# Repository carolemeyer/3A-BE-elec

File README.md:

# 3A-BE-elec
BE d'électronique de 3AE du binôme : Carole Meyer et Louis Nouguerède

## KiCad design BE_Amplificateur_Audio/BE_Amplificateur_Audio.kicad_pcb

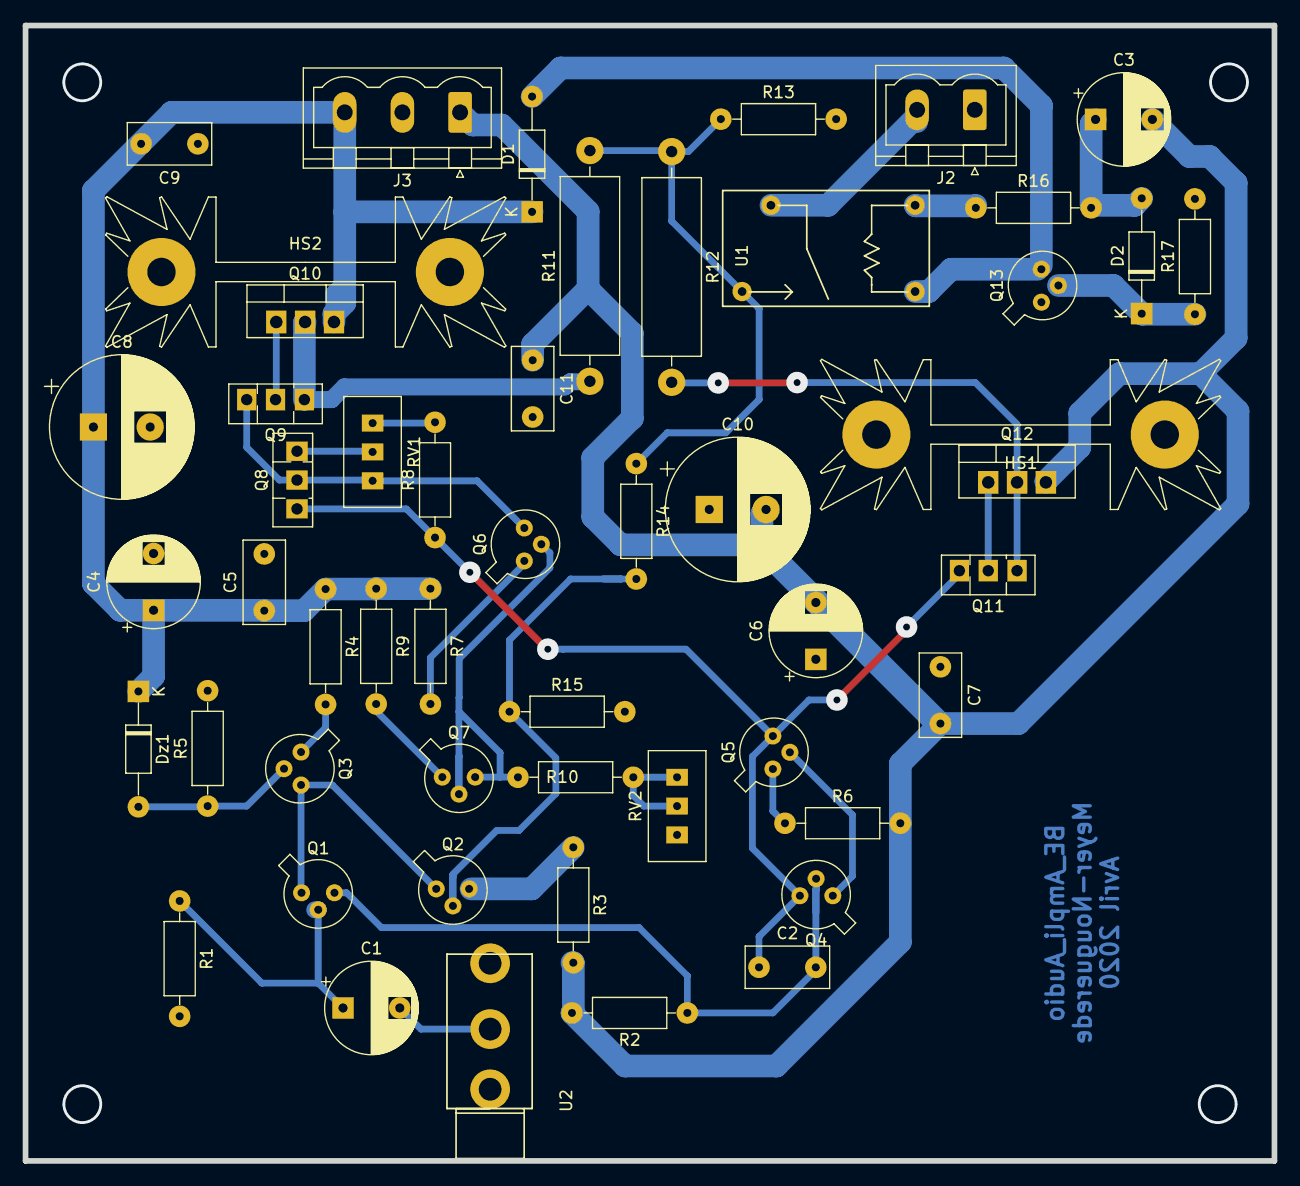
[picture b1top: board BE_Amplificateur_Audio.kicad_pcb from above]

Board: 2 copper layers, 110.0 x 100.0 mm, 52 parts (0 on the bottom side), 31 nets.

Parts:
C1, C3: 47µ; CP_Radial_D8.0mm_P5.00mm
C2: C; C_Rect_L7.2mm_W3.5mm_P5.00mm_FKS2_FKP2_MKS2_MKP2
C4, C6: 10µ; CP_Radial_D8.0mm_P5.00mm
C5, C7, C9, C11: 100n; C_Rect_L7.2mm_W3.5mm_P5.00mm_FKS2_FKP2_MKS2_MKP2
C8, C10: 470µ; CP_Radial_D12.5mm_P5.00mm
D1, D2: 1N4148; D_DO-35_SOD27_P10.16mm_Horizontal
Dz1: BZX55C5V1; D_DO-35_SOD27_P10.16mm_Horizontal
HS1, HS2: Heatsink; Heatsink_Fischer_SK104-STC-STIC_35x13mm_2xDrill2.5mm
J2: Conn_01x02; PhoenixContact_MSTBVA_2,5_2-G-5,08_1x02_P5.08mm_Vertical
J3: Conn_01x03; PhoenixContact_MSTBVA_2,5_3-G-5,08_1x03_P5.08mm_Vertical
Q1, Q2, Q3, Q6, Q7: 2N2907; TO-18-3
Q4, Q5, Q13: 2N2222; TO-18-3
Q8, Q9: BD139; TO-126-3_Vertical
Q10: TIP32; TO-220-3_Vertical
Q11: BD138; TO-126-3_Vertical
Q12: TIP31; TO-220-3_Vertical
R1, R2, R3, R4, R5, R6, R7, R8, R9, R10, R13, R14, R15, R16, R17: R; R_Axial_DIN0207_L6.3mm_D2.5mm_P10.16mm_Horizontal
R11, R12: R; R_Axial_DIN0516_L15.5mm_D5.0mm_P20.32mm_Horizontal
RV1, RV2: R_POT; Potentiometer_Bourns_3296W_Vertical
U1: Relay_1CT; RelayBE
U2: Jack_Mono; Jack_35RAPC2AV

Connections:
+12V: C4.1, C5.1, C8.1, C9.2, D1.1, Dz1.1, J3.3, Q10.3, R4.1, R7.1, R9.1
-12V: C3.2, C6.2, C7.2, C10.2, C11.1, J3.1, Q12.3, R2.2, R3.2, R6.2
GND: C4.2, C5.2, C6.1, C7.1, C8.2, C9.1, C10.1, C11.2, J2.1, J3.2, Q13.1, R1.2, R5.2, R13.2, R15.2, R17.2, RV2.3, U2.G
unnamed: C1.1, Q1.2, R1.1
unnamed: C1.2, U2.T
unnamed: C2.1, Q4.3, Q5.3, Q8.1, Q11.3, R8.1
unnamed: C2.2, Q1.3, Q4.2, R2.1
unnamed: C3.1, D2.2, R16.2
unnamed: D1.2, Q13.3, U1.6
unnamed: D2.1, Q13.2, R17.1
unnamed: Dz1.2, Q3.2, R5.1
unnamed: J2.2, U1.1
unnamed: Q1.1, Q2.1, Q3.3
unnamed: Q2.2, R14.2, R15.1
unnamed: Q2.3, R3.1
unnamed: Q3.1, R4.2
unnamed: Q4.1, Q5.2
unnamed: Q5.1, R6.1
unnamed: Q6.1, R7.2
unnamed: Q6.2, Q7.2, Q7.3, R10.1
unnamed: Q6.3, Q8.2, Q9.3, RV1.1
unnamed: Q7.1, R9.2
unnamed: Q8.3, RV1.2
unnamed: Q9.2, Q10.1
unnamed: Q9.1, Q10.2, R11.1
unnamed: Q11.1, Q12.2, R12.2
unnamed: Q11.2, Q12.1
unnamed: R8.2, RV1.3
unnamed: R10.2, RV2.1, RV2.2
unnamed: R11.2, R12.1, R13.1, R14.1, U1.7
unnamed: R16.1, U1.2

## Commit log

2020-03-20 Upload of Kicad schematic
    Mise en ligne des fichiers de Kicad pour le routage. Seul le schematic est fait à ce jour. Vérifier certains composants, notés ACHANGER.
2020-03-21 màj schematic + empreintes
    Modification du schematic pour coller avec les instructions données.
    Tentative de match des empreintes : à vérifier. Apparemment la lib d'empreinte donnée par le prof ne s'est pas chargée correctement : à vérfier !
2020-03-21 màj empreintes
    Empreintes màj. A verifier qd même pour voir si la lib du prof a bien marché.
    A faire : empreinte du relai.
2020-03-23 màj empreintes
    manque à faire l'empreinte du relai
2020-03-23 empreinte du relai: ok
2020-03-24 Màj test
    J'ai fait un test pour mettre en ligne
2020-04-19 Placement + Routage
    Placement + routage (v0 à v2)
2020-04-19 MAJ jack down or side?
    Is it possible to put the jack on the side?
2020-04-22 PRET POUR VERIF
    Problème de librairie de symboles qui est apparu --> résolu
    Schematic à jour.
    Netliste à jour.
    Placement à jour.
    Routage à jour.
    Prêt pour vérification du placement et routage.
2020-04-23 PRET POUR VERIF
2020-04-23 Modifs après avis
    Modifications après 1er avis de placement et routage
2020-04-24 Corrections au niveau de Q7
    J'ai corrigé les PWRFLAG et trouvé une erreur au niveau de Q7 : il manquait un fil. C'est corrigé et le routage est mis à jour.
2020-05-10 ROUTAGE TERMINE
